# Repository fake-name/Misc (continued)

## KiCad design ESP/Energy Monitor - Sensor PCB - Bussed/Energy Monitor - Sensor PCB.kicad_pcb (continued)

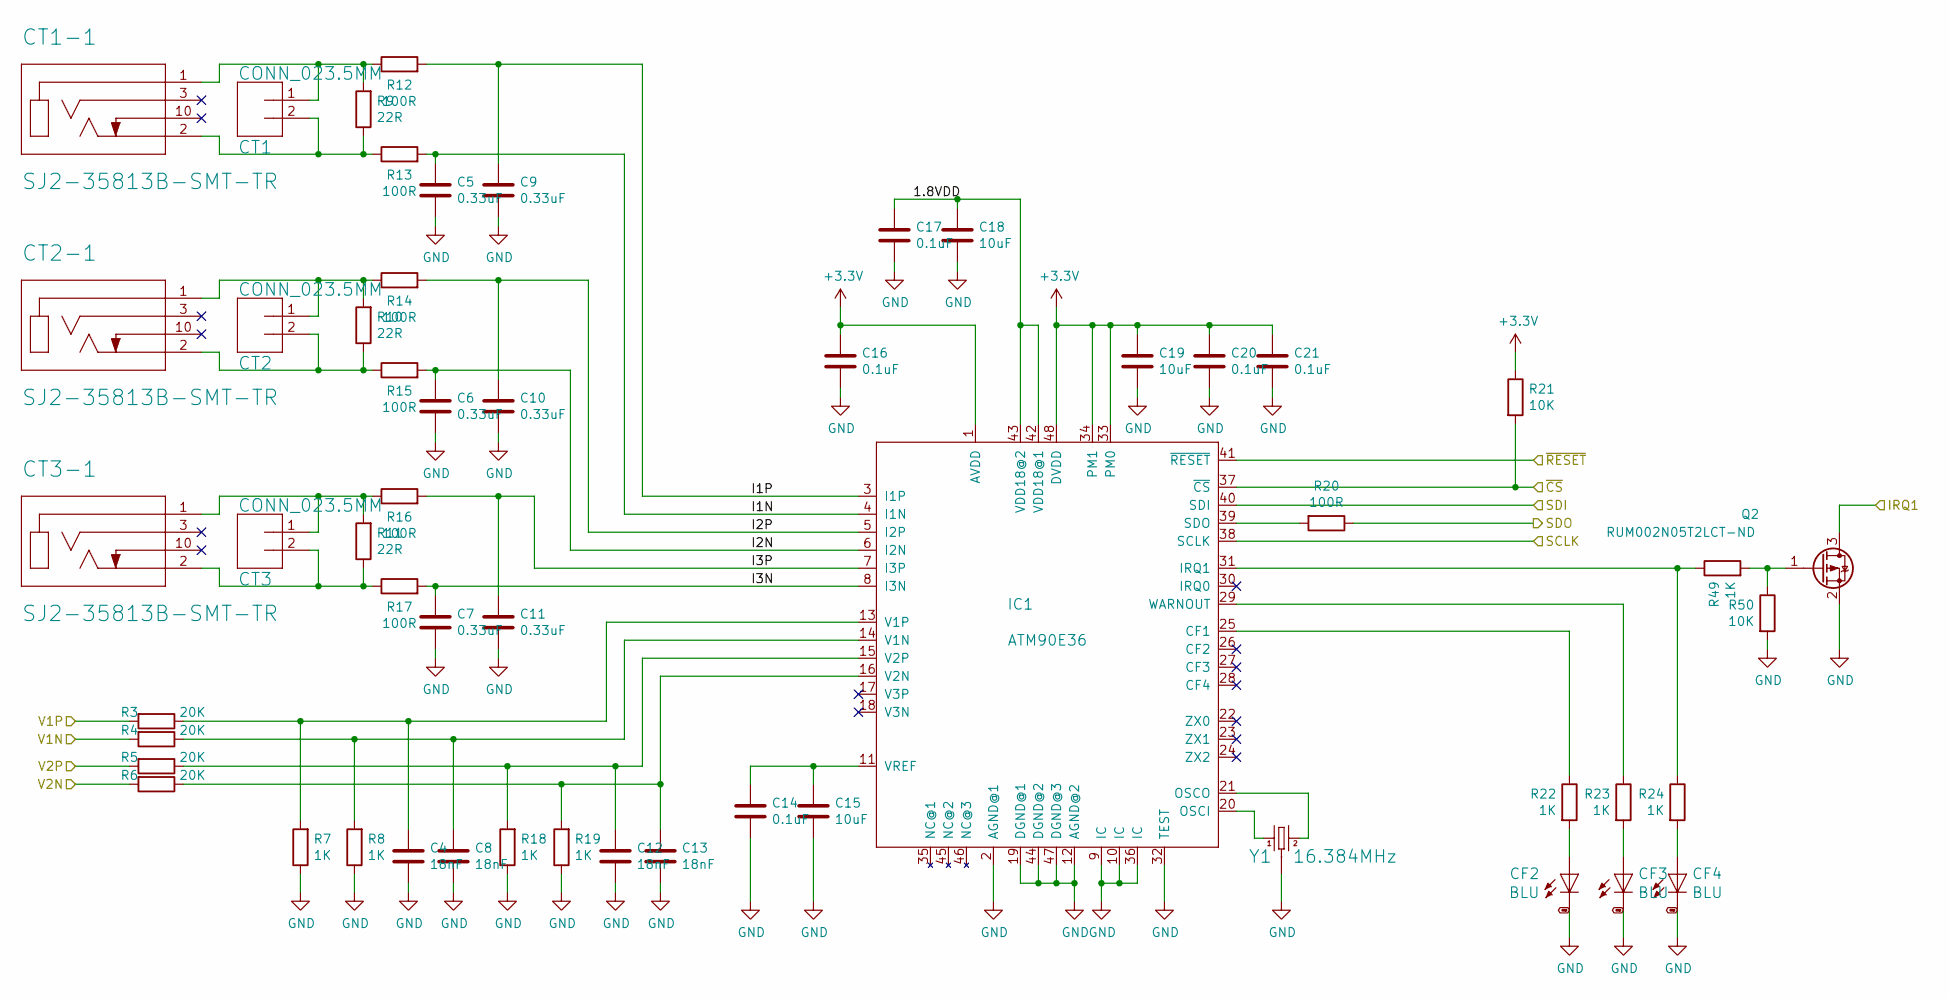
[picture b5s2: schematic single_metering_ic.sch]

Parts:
C4, C8, C12, C13: 18nF; C_0603_1608Metric_Pad1.05x0.95mm_HandSolder
C5, C6, C7, C9, C10, C11: 0.33uF; C_0603_1608Metric_Pad1.05x0.95mm_HandSolder
C14, C16, C17, C20, C21: 0.1uF; C_0603_1608Metric_Pad1.05x0.95mm_HandSolder
C15, C18, C19: 10uF; C_1206_3216Metric_Pad1.42x1.75mm_HandSolder
CF2, CF3, CF4: BLU; CHIPLED_0603
CT1, CT2, CT3: CONN_023.5MM; SCREWTERMINAL-3.5MM-2
CT1-1, CT2-1, CT3-1: SJ2-35813B-SMT-TR; CUI_SJ2-35813B-SMT-TR
IC1: ATM90E36; QFP50P900X900X120-48
Q2: RUM002N05T2LCT-ND; SOT-723
R3, R4, R5, R6: 20K; R_0603_1608Metric_Pad1.05x0.95mm_HandSolder
R7, R8, R18, R19, R22, R23, R24, R49: 1K; R_0603_1608Metric_Pad1.05x0.95mm_HandSolder
R9, R10, R11: 22R; R_0603_1608Metric_Pad1.05x0.95mm_HandSolder
R12, R13, R14, R15, R16, R17, R20: 100R; R_0603_1608Metric_Pad1.05x0.95mm_HandSolder
R21, R50: 10K; R_0603_1608Metric_Pad1.05x0.95mm_HandSolder
Y1: 16.384MHz; CRYSTAL-SMD-3.2X2.5MM

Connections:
+3V3: C16.1, C19.1, C20.1, C21.1, IC1.1 (AVDD), IC1.33 (PM0), IC1.34 (PM1), IC1.48 (DVDD), R21.1; also elsewhere on the board
/INT_1: Q2.3 (D); also elsewhere on the board
/meter_1/1.8VDD: C17.1, C18.1, IC1.42 (VDD18@1), IC1.43 (VDD18@2)
/meter_1/I1N: C5.1, IC1.4 (I1N), R13.2
/meter_1/I1P: C9.1, IC1.3 (I1P), R12.2
/meter_1/I2N: C6.1, IC1.6 (I2N), R15.2
/meter_1/I2P: C10.1, IC1.5 (I2P), R14.2
/meter_1/I3N: C7.1, IC1.8 (I3N), R17.2
/meter_1/I3P: C11.1, IC1.7 (I3P), R16.2
/meter_1/SCLK: IC1.38 (SCLK); also elsewhere on the board
/meter_1/SDI: IC1.40 (SDI); also elsewhere on the board
/meter_1/SDO: R20.1; also elsewhere on the board
/meter_1/V1N: R4.2; also elsewhere on the board
/meter_1/V1P: R3.2; also elsewhere on the board
/meter_1/V2N: R6.2; also elsewhere on the board
/meter_1/V2P: R5.2; also elsewhere on the board
/meter_1/~CS: IC1.37 (~CS), R21.2; also elsewhere on the board
/meter_1/~RESET: IC1.41 (~RESET); also elsewhere on the board
GND: C4.2, C5.2, C6.2, C7.2, C8.2, C9.2, C10.2, C11.2, C12.2, C13.2, C14.2, C15.2, C16.2, C17.2, C18.2, C19.2, C20.2, C21.2, CF2.C, CF3.C, CF4.C, IC1.2 (AGND@1), IC1.9 (IC), IC1.10 (IC), IC1.12 (AGND@2), IC1.19 (DGND@1), IC1.32 (TEST), IC1.36 (IC), IC1.44 (DGND@2), IC1.47 (DGND@3), Q2.2 (S), R7.1, R8.1, R18.1, R19.1, R50.2, Y1.2 (3), Y1.4 (3); also elsewhere on the board
unnamed: C4.1, IC1.13 (V1P), R3.1, R7.2
unnamed: C8.1, IC1.14 (V1N), R4.1, R8.2
unnamed: C12.1, IC1.15 (V2P), R5.1, R18.2
unnamed: C13.1, IC1.16 (V2N), R6.1, R19.2
unnamed: C14.1, C15.1, IC1.11 (VREF)
unnamed: CF2.A, R22.2
unnamed: CF3.A, R23.2
unnamed: CF4.A, R24.2
unnamed: CT1.1, CT1-1.1 (SLEEVE), R9.2, R12.1
unnamed: CT1.2, CT1-1.2 (TIP), R9.1, R13.1
unnamed: CT2.1, CT2-1.1 (SLEEVE), R10.2, R14.1
unnamed: CT2.2, CT2-1.2 (TIP), R10.1, R15.1
unnamed: CT3.1, CT3-1.1 (SLEEVE), R11.2, R16.1
unnamed: CT3.2, CT3-1.2 (TIP), R11.1, R17.1
unnamed: IC1.20 (OSCI), Y1.1
unnamed: IC1.21 (OSCO), Y1.3 (2)
unnamed: IC1.25 (CF1), R22.1
unnamed: IC1.29 (WARNOUT), R23.1
unnamed: IC1.31 (IRQ1), R24.1, R49.1
unnamed: IC1.39 (SDO), R20.2
unnamed: Q2.1 (G), R49.2, R50.1

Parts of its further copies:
C22, C26, C30, C31: 18nF; C_0603_1608Metric_Pad1.05x0.95mm_HandSolder
C23, C24, C25, C27, C28, C29: 0.33uF; C_0603_1608Metric_Pad1.05x0.95mm_HandSolder
C32, C34, C35, C38, C39: 0.1uF; C_0603_1608Metric_Pad1.05x0.95mm_HandSolder
C33, C36, C37: 10uF; C_1206_3216Metric_Pad1.42x1.75mm_HandSolder
CF5, CF6, CF7: BLU; CHIPLED_0603
CT1-2, CT2-2, CT3-2: SJ2-35813B-SMT-TR; CUI_SJ2-35813B-SMT-TR
CT4, CT5, CT6: CONN_023.5MM; SCREWTERMINAL-3.5MM-2
IC2: ATM90E36; QFP50P900X900X120-48
Q3: RUM002N05T2LCT-ND; SOT-723
R25, R26, R27, R28: 20K; R_0603_1608Metric_Pad1.05x0.95mm_HandSolder
R29, R30, R40, R41, R44, R45, R46, R51: 1K; R_0603_1608Metric_Pad1.05x0.95mm_HandSolder
R31, R32, R33: 22R; R_0603_1608Metric_Pad1.05x0.95mm_HandSolder
R34, R35, R36, R37, R38, R39, R42: 100R; R_0603_1608Metric_Pad1.05x0.95mm_HandSolder
R43, R52: 10K; R_0603_1608Metric_Pad1.05x0.95mm_HandSolder
Y2: 16.384MHz; CRYSTAL-SMD-3.2X2.5MM

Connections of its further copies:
+3V3: C34.1, C37.1, C38.1, C39.1, IC2.1 (AVDD), IC2.33 (PM0), IC2.34 (PM1), IC2.48 (DVDD), R43.1; also elsewhere on the board
/INT_2: Q3.3 (D); also elsewhere on the board
/meter_1/SCLK: IC2.38 (SCLK); also elsewhere on the board
/meter_1/SDI: IC2.40 (SDI); also elsewhere on the board
/meter_1/SDO: R42.1; also elsewhere on the board
/meter_1/V1N: R26.2; also elsewhere on the board
/meter_1/V1P: R25.2; also elsewhere on the board
/meter_1/V2N: R28.2; also elsewhere on the board
/meter_1/V2P: R27.2; also elsewhere on the board
/meter_1/~RESET: IC2.41 (~RESET); also elsewhere on the board
/meter_2/1.8VDD: C35.1, C36.1, IC2.42 (VDD18@1), IC2.43 (VDD18@2)
/meter_2/I1N: C23.1, IC2.4 (I1N), R35.2
/meter_2/I1P: C27.1, IC2.3 (I1P), R34.2
/meter_2/I2N: C24.1, IC2.6 (I2N), R37.2
/meter_2/I2P: C28.1, IC2.5 (I2P), R36.2
/meter_2/I3N: C25.1, IC2.8 (I3N), R39.2
/meter_2/I3P: C29.1, IC2.7 (I3P), R38.2
/meter_2/~CS: IC2.37 (~CS), R43.2; also elsewhere on the board
GND: C22.2, C23.2, C24.2, C25.2, C26.2, C27.2, C28.2, C29.2, C30.2, C31.2, C32.2, C33.2, C34.2, C35.2, C36.2, C37.2, C38.2, C39.2, CF5.C, CF6.C, CF7.C, IC2.2 (AGND@1), IC2.9 (IC), IC2.10 (IC), IC2.12 (AGND@2), IC2.19 (DGND@1), IC2.32 (TEST), IC2.36 (IC), IC2.44 (DGND@2), IC2.47 (DGND@3), Q3.2 (S), R29.1, R30.1, R40.1, R41.1, R52.2, Y2.2 (3), Y2.4 (3); also elsewhere on the board
unnamed: C22.1, IC2.13 (V1P), R25.1, R29.2
unnamed: C26.1, IC2.14 (V1N), R26.1, R30.2
unnamed: C30.1, IC2.15 (V2P), R27.1, R40.2
unnamed: C31.1, IC2.16 (V2N), R28.1, R41.2
unnamed: C32.1, C33.1, IC2.11 (VREF)
unnamed: CF5.A, R44.2
unnamed: CF6.A, R45.2
unnamed: CF7.A, R46.2
unnamed: CT1-2.1 (SLEEVE), CT4.1, R31.2, R34.1
unnamed: CT1-2.2 (TIP), CT4.2, R31.1, R35.1
unnamed: CT2-2.1 (SLEEVE), CT5.1, R32.2, R36.1
unnamed: CT2-2.2 (TIP), CT5.2, R32.1, R37.1
unnamed: CT3-2.1 (SLEEVE), CT6.1, R33.2, R38.1
unnamed: CT3-2.2 (TIP), CT6.2, R33.1, R39.1
unnamed: IC2.20 (OSCI), Y2.1
unnamed: IC2.21 (OSCO), Y2.3 (2)
unnamed: IC2.25 (CF1), R44.1
unnamed: IC2.29 (WARNOUT), R45.1
unnamed: IC2.31 (IRQ1), R46.1, R51.1
unnamed: IC2.39 (SDO), R42.2
unnamed: Q3.1 (G), R51.2, R52.1

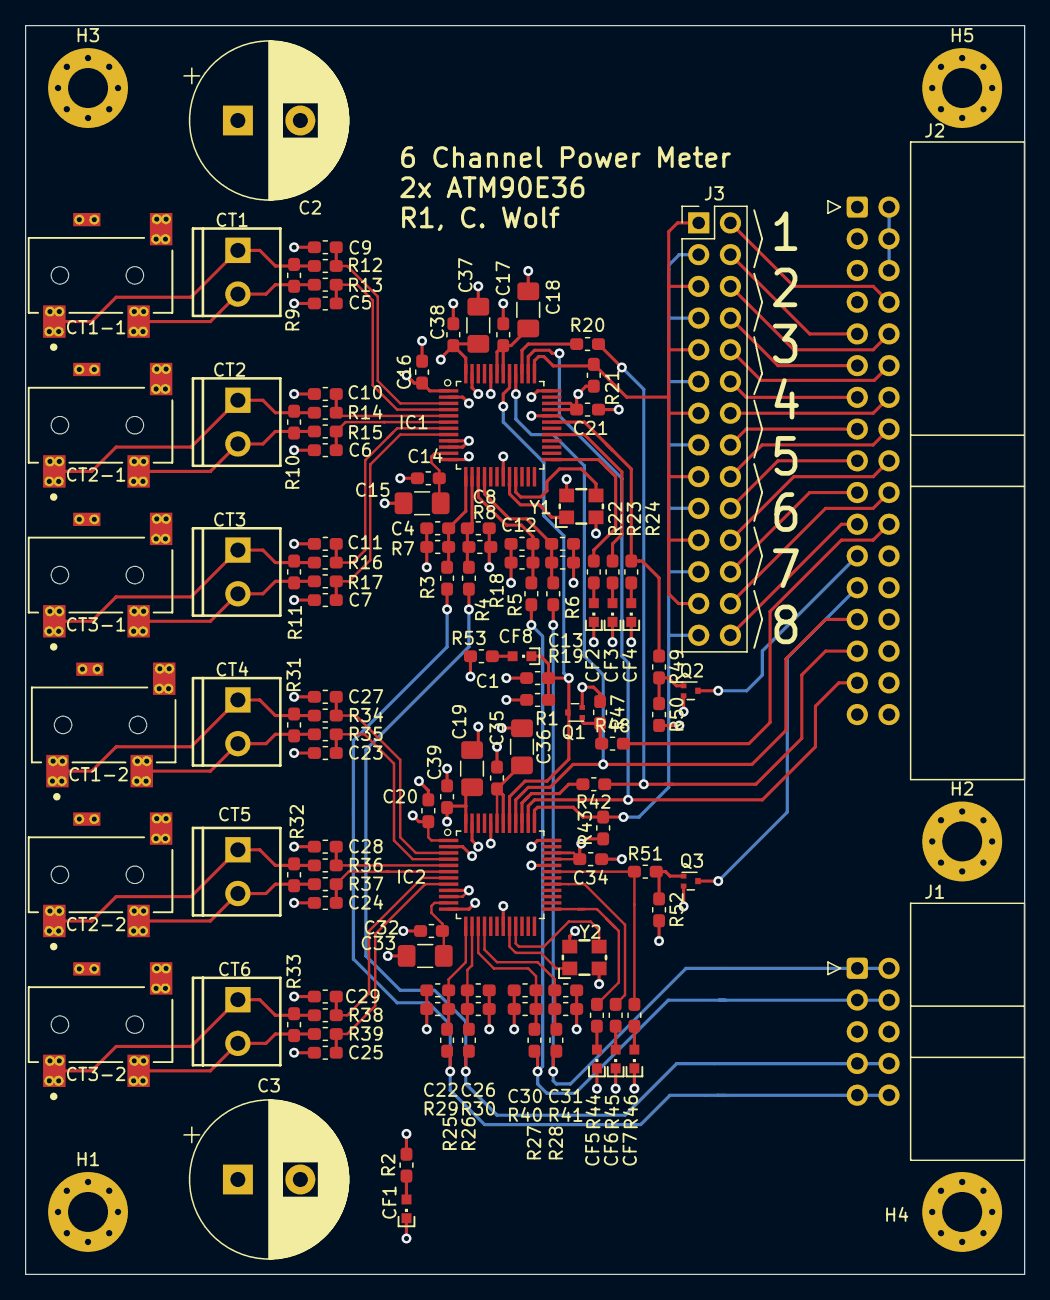
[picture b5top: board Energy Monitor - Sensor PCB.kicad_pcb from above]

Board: 4 copper layers, 80.0 x 100.0 mm, 127 parts (0 on the bottom side), 89 nets.

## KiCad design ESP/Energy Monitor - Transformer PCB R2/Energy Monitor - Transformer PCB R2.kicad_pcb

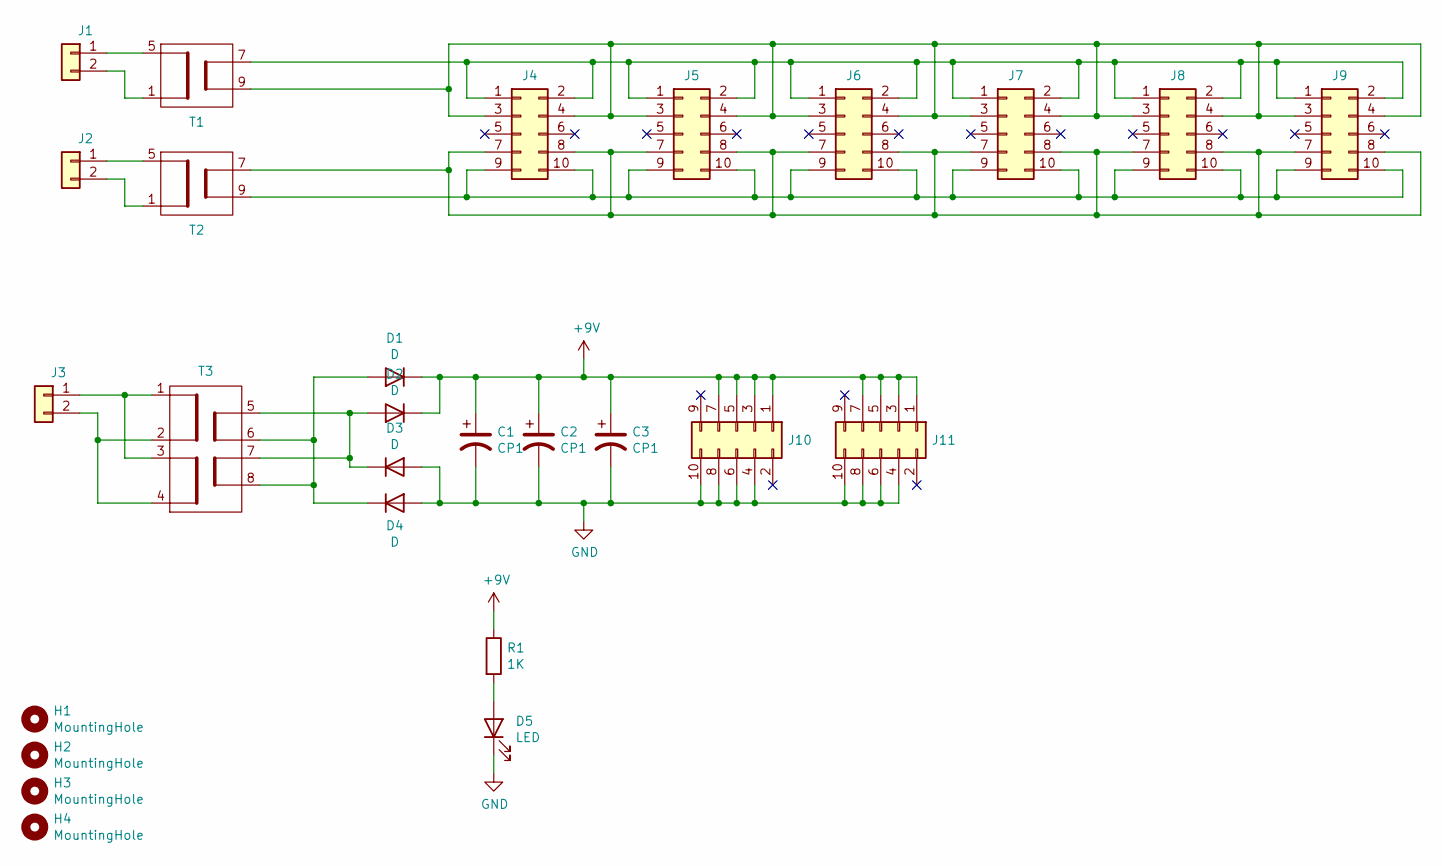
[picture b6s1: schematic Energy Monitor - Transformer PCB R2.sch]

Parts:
C1, C2, C3: CP1; CP_Radial_D12.5mm_P5.00mm
D1, D2, D3, D4: D; D_DO-41_SOD81_P12.70mm_Horizontal
D5: LED; LED_D5.0mm_Clear
H1, H2, H3, H4: MountingHole; MountingHole_3.2mm_M3_Pad_Via
J1, J2, J3: Conn_01x02; WE 691411410002 - 2 Pin Wire-To-Board Terminal Block
J4, J5, J6, J7, J8, J9, J10, J11: Conn_02x05_Odd_Even; IDC-Header_2x05_P2.54mm_Vertical
R1: 1K; R_Axial_DIN0309_L9.0mm_D3.2mm_P15.24mm_Horizontal
T1, T2: EI30-15.5; EI30-15.5-TH
T3: AHI050; AHI050-TH

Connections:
+9V: C1.1, C2.1, C3.1, D1.1 (K), D2.1 (K), J10.1, J10.3, J10.5, J10.7, J11.1, J11.3, J11.5, J11.7, R1.1
GND: C1.2, C2.2, C3.2, D3.2 (A), D4.2 (A), D5.1 (K), J10.4, J10.6, J10.8, J10.10, J11.4, J11.6, J11.8, J11.10
unnamed: D1.2 (A), D4.1 (K), T3.6, T3.8
unnamed: D2.2 (A), D3.1 (K), T3.5, T3.7
unnamed: D5.2 (A), R1.2
unnamed: J1.1, T1.5
unnamed: J1.2, T1.1
unnamed: J2.1, T2.5
unnamed: J2.2, T2.1
unnamed: J3.1, T3.1, T3.3
unnamed: J3.2, T3.2, T3.4
unnamed: J4.1, J4.2, J5.1, J5.2, J6.1, J6.2, J7.1, J7.2, J8.1, J8.2, J9.1, J9.2, T1.7
unnamed: J4.3, J4.4, J5.3, J5.4, J6.3, J6.4, J7.3, J7.4, J8.3, J8.4, J9.3, J9.4, T1.9
unnamed: J4.7, J4.8, J5.7, J5.8, J6.7, J6.8, J7.7, J7.8, J8.7, J8.8, J9.7, J9.8, T2.7
unnamed: J4.9, J4.10, J5.9, J5.10, J6.9, J6.10, J7.9, J7.10, J8.9, J8.10, J9.9, J9.10, T2.9

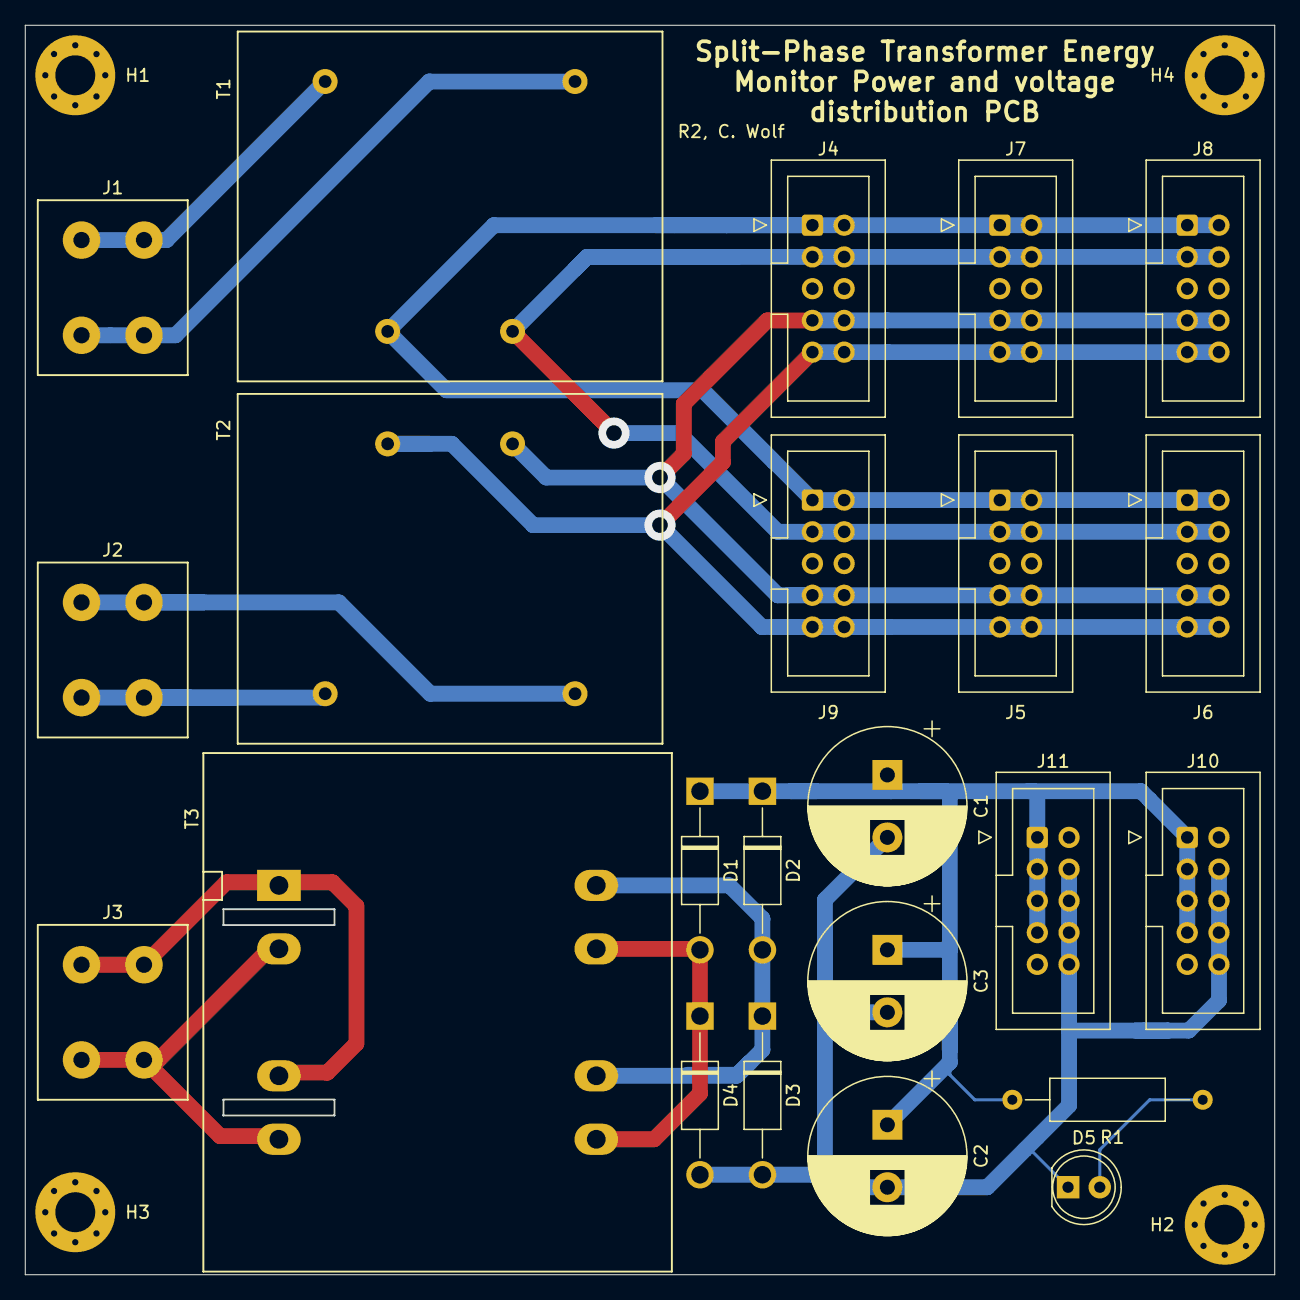
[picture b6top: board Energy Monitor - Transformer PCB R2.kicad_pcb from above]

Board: 2 copper layers, 100.0 x 100.0 mm, 27 parts (0 on the bottom side), 15 nets.

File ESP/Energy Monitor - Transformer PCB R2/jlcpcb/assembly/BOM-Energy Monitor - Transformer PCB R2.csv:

Comment,Designator,Footprint,LCSC
AHI050,T3,AHI050-TH,
EI30-15.5,T2,EI30-15.5-TH,
D,D2,D_DO-41_SOD81_P12.70mm_Horizontal,
EI30-15.5,T1,EI30-15.5-TH,
CP1,C3,CP_Radial_D12.5mm_P5.00mm,
Conn_02x05_Odd_Even,J11,IDC-Header_2x05_P2.54mm_Vertical,
1K,R1,R_Axial_DIN0309_L9.0mm_D3.2mm_P15.24mm_Horizontal,
LED,D5,LED_D5.0mm_Clear,
Conn_02x05_Odd_Even,J9,IDC-Header_2x05_P2.54mm_Vertical,
Conn_02x05_Odd_Even,J8,IDC-Header_2x05_P2.54mm_Vertical,
Conn_02x05_Odd_Even,J7,IDC-Header_2x05_P2.54mm_Vertical,
Conn_02x05_Odd_Even,J6,IDC-Header_2x05_P2.54mm_Vertical,
Conn_02x05_Odd_Even,J10,IDC-Header_2x05_P2.54mm_Vertical,
Conn_02x05_Odd_Even,J5,IDC-Header_2x05_P2.54mm_Vertical,
Conn_02x05_Odd_Even,J4,IDC-Header_2x05_P2.54mm_Vertical,
D,D4,D_DO-41_SOD81_P12.70mm_Horizontal,
D,D3,D_DO-41_SOD81_P12.70mm_Horizontal,
D,D1,D_DO-41_SOD81_P12.70mm_Horizontal,
CP1,C2,CP_Radial_D12.5mm_P5.00mm,
CP1,C1,CP_Radial_D12.5mm_P5.00mm,
Conn_01x02,J3,WE 691411410002 - 2 Pin Wire-To-Board Terminal Block,
Conn_01x02,J2,WE 691411410002 - 2 Pin Wire-To-Board Terminal Block,
Conn_01x02,J1,WE 691411410002 - 2 Pin Wire-To-Board Terminal Block,
